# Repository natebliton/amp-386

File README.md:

# amp-386
This is a quick PCB of an LM386 circuit I found here:
https://www.homemade-circuits.com/ic-lm-386-datasheet-explained-in-simple/

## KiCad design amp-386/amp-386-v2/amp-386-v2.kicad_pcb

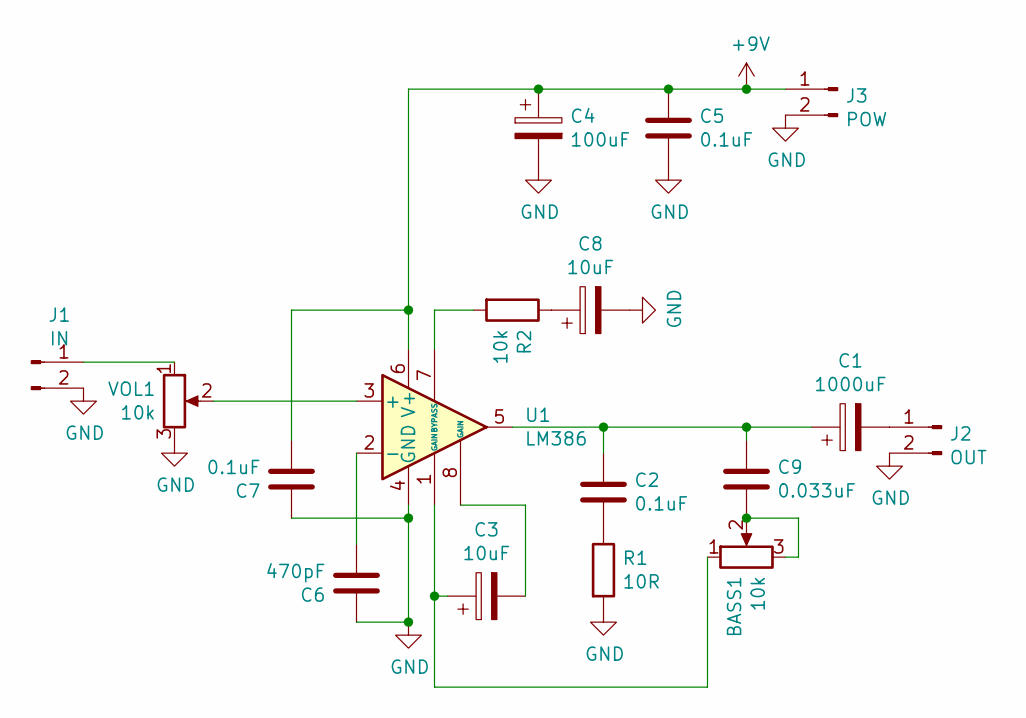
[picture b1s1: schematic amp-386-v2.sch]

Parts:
BASS1: 10k; PinHeader_1x03_P2.54mm_Vertical
C1: 1000uF; CP_Radial_D5.0mm_P2.50mm
C2, C5, C7: 0.1uF; C_Disc_D4.3mm_W1.9mm_P5.00mm
C3, C8: 10uF; CP_Radial_D5.0mm_P2.50mm
C4: 100uF; CP_Radial_D5.0mm_P2.50mm
C6: 470pF; C_Disc_D4.3mm_W1.9mm_P5.00mm
C9: 0.033uF; C_Disc_D4.3mm_W1.9mm_P5.00mm
J1: IN; PinHeader_1x02_P2.54mm_Vertical
J2: OUT; PinHeader_1x02_P2.54mm_Vertical
J3: POW; PinHeader_1x02_P2.54mm_Vertical
R1: 10R; R_Axial_DIN0207_L6.3mm_D2.5mm_P10.16mm_Horizontal
R2: 10k; R_Axial_DIN0207_L6.3mm_D2.5mm_P10.16mm_Horizontal
U1: LM386; DIP-8_W7.62mm_Socket_LongPads
VOL1: 10k; PinHeader_1x03_P2.54mm_Vertical

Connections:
+9V: C4.1, C5.1, C7.2, J3.1, U1.6 (V+)
GND: C4.2, C5.2, C6.1, C7.1, C8.2, J1.2, J2.2, J3.2, R1.2, U1.4 (GND), VOL1.3
unnamed: BASS1.1, C3.1, U1.1 (GAIN)
unnamed: BASS1.2, BASS1.3, C9.2
unnamed: C1.1, C2.1, C9.1, U1.5
unnamed: C1.2, J2.1
unnamed: C2.2, R1.1
unnamed: C3.2, U1.8 (GAIN)
unnamed: C6.2, U1.2 (-)
unnamed: C8.1, R2.1
unnamed: J1.1, VOL1.1
unnamed: R2.2, U1.7 (BYPASS)
unnamed: U1.3 (+), VOL1.2

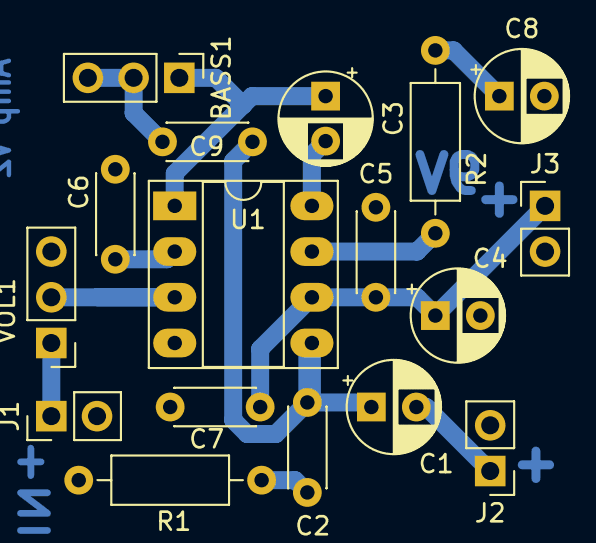
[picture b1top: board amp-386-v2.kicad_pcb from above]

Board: 2 copper layers, 17 parts (0 on the bottom side), 13 nets.

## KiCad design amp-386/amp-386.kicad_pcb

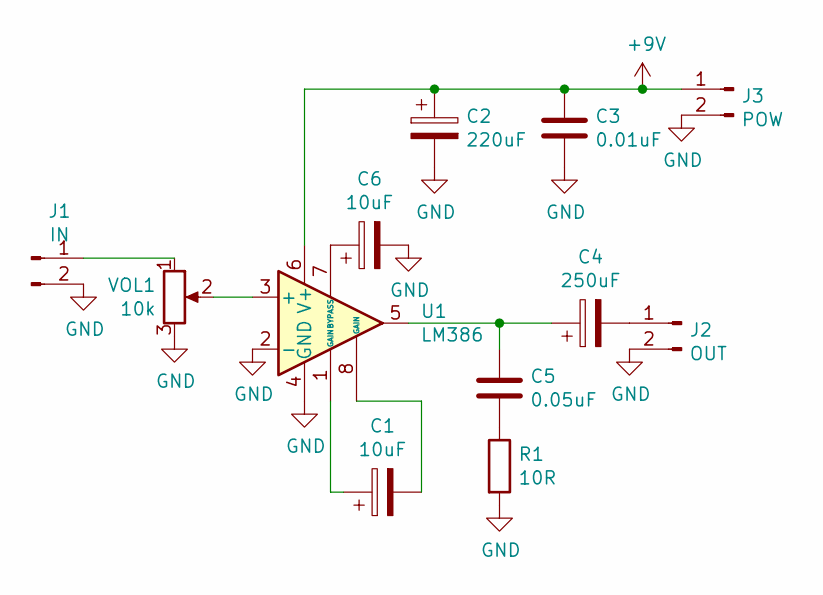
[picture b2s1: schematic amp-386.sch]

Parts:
C1, C6: 10uF; CP_Radial_D5.0mm_P2.50mm
C2: 220uF; CP_Radial_D5.0mm_P2.50mm
C3: 0.01uF; C_Disc_D4.3mm_W1.9mm_P5.00mm
C4: 250uF; CP_Radial_D5.0mm_P2.50mm
C5: 0.05uF; C_Disc_D4.3mm_W1.9mm_P5.00mm
J1: IN; PinHeader_1x02_P2.54mm_Vertical
J2: OUT; PinHeader_1x02_P2.54mm_Vertical
J3: POW; PinHeader_1x02_P2.54mm_Vertical
R1: 10R; R_Axial_DIN0207_L6.3mm_D2.5mm_P10.16mm_Horizontal
U1: LM386; DIP-8_W7.62mm_Socket_LongPads
VOL1: 10k; PinHeader_1x03_P2.54mm_Vertical

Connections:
+9V: C2.1, C3.1, J3.1, U1.6 (V+)
GND: C2.2, C3.2, C6.2, J1.2, J2.2, J3.2, R1.2, U1.2 (-), U1.4 (GND), VOL1.3
unnamed: C1.1, U1.1 (GAIN)
unnamed: C1.2, U1.8 (GAIN)
unnamed: C4.1, C5.1, U1.5
unnamed: C4.2, J2.1
unnamed: C5.2, R1.1
unnamed: C6.1, U1.7 (BYPASS)
unnamed: J1.1, VOL1.1
unnamed: U1.3 (+), VOL1.2

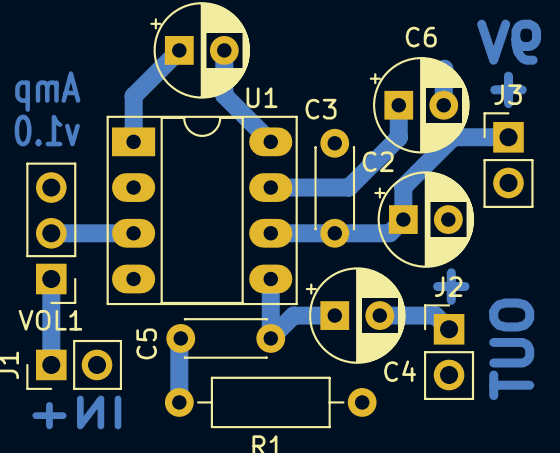
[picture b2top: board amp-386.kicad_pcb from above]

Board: 2 copper layers, 12 parts (0 on the bottom side), 10 nets.

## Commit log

2020-11-19 initial version in KiCad
2020-12-11 found better shematic on circuitbasics
2020-12-11 new layout with better schematic
